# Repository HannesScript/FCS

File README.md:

# FCS - Flight Control System

This is a software designed for my own rocket's flight computer which is based on the ESP32-S3.

## Requirements:

- rust
- cargo
- espup - install with `cargo install espup && espup install`
- espflash - install with `cargo install espflash --version 3.3.0`

You can just run the [setup.sh](./setup.sh) file.

## Build & Flash:

You can just run [build_and_flash.sh](./build_and_flash.sh).

## Components:

- ESP32-S3
- BMP280
- MPU6050
- PCA9685
- nRF24L01
- Arduino (ESP32-S3) compatible SD-Card reader
- a GPS module (e.g. GY-GPS6MV2)
- 2x simple N-MOSFET (though please check if it is usable with a chip such as this)
- DHT11

## PCB:

All the files for the PCB and the schematics are located in the [pcb folder](./pcb/). These files are ready for manufacturing and usage.

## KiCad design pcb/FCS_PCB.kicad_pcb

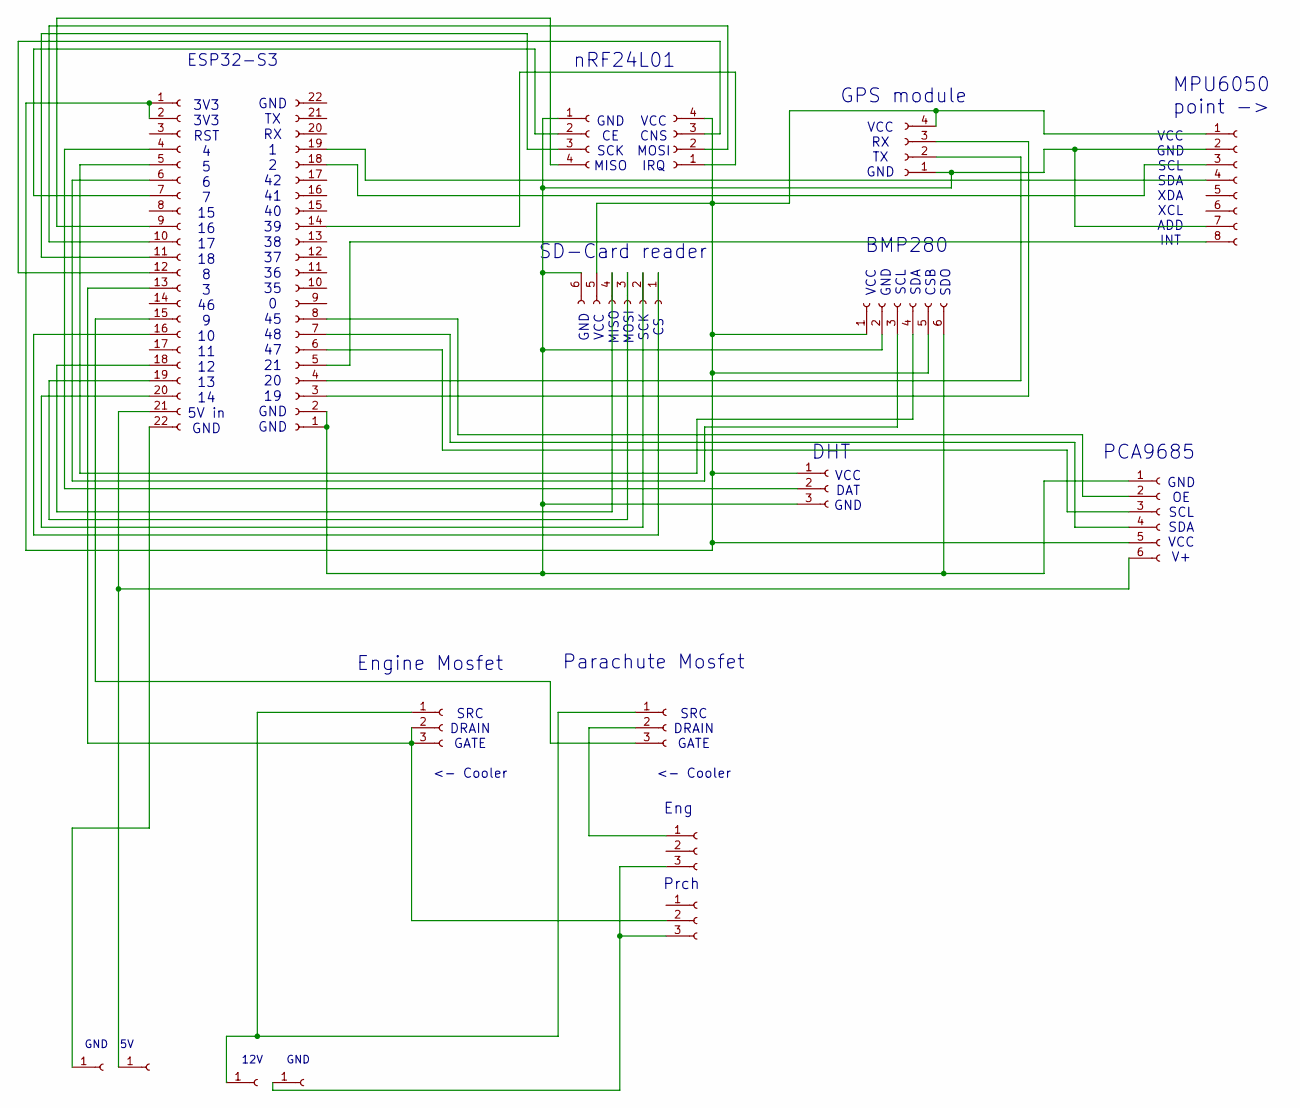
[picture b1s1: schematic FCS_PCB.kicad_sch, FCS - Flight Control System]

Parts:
J1, J2: Conn_01x22_Socket; PinSocket_1x22_P2.54mm_Vertical
J3, J4, J6: Conn_01x04_Socket; PinSocket_1x04_P2.54mm_Vertical
J5: PinSocket_1x06_P2.54mm_Vertical
J7, J10: Conn_01x06_Socket; PinSocket_1x06_P2.54mm_Vertical
J8: Conn_01x08_Socket; PinSocket_1x08_P2.54mm_Vertical
J9, J11, J12, J13, J14: Conn_01x03_Socket; PinSocket_1x03_P2.54mm_Vertical
J15, J16, J17, J18: Conn_01x01_Socket; PinSocket_1x01_P2.00mm_Vertical

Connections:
unnamed: J1.1, J1.2, J4.4, J5.5, J6.4, J7.1, J7.5, J8.1, J9.1, J10.5
unnamed: J1.4, J9.2
unnamed: J1.5, J7.4
unnamed: J1.6, J7.3
unnamed: J1.7, J3.2
unnamed: J1.9, J3.4
unnamed: J1.10, J4.2
unnamed: J1.11, J3.3
unnamed: J1.12, J4.3
unnamed: J1.13, J11.2, J11.3, J14.2
unnamed: J1.15, J12.3
unnamed: J1.16, J5.1
unnamed: J1.18, J5.4
unnamed: J1.19, J5.3
unnamed: J1.20, J5.2
unnamed: J1.21, J10.6, J16.1
unnamed: J1.22, J15.1
unnamed: J2.3, J6.3
unnamed: J2.4, J6.2
unnamed: J2.5, J8.8
unnamed: J2.14, J4.1
unnamed: J2.18, J8.3
unnamed: J2.19, J8.4
unnamed: J2.1, J2.2, J3.1, J5.6, J6.1, J7.2, J7.6, J8.2, J8.7, J9.3, J10.1
unnamed: J2.8, J10.2
unnamed: J2.6, J10.3
unnamed: J2.7, J10.4
unnamed: J11.1, J12.1, J17.1
unnamed: J12.2, J13.1
unnamed: J13.3, J14.3, J18.1

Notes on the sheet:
3V3 3V3 RST 4 5 6 7 15 16 17 18 8 3 46 9 10 11 12 13 14 5V in GND
nRF24L01
Parachute Mosfet
Eng
VCC GND SCL SDA XDA XCL ADD INT
VCC DAT GND
ESP32-S3
SD-Card reader
BMP280
GND CE SCK MISO
GPS module
GND OE SCL SDA VCC V+
Prch
VCC CNS MOSI IRQ
Engine Mosfet
12V GND
VCC GND SCL SDA CSB SDO
PCA9685
GND 5V
VCC RX TX GND
SRC DRAIN GATE <- Cooler
MPU6050 point ->
GND VCC MISO MOSI SCK CS
DHT
GND TX RX 1 2 42 41 40 39 38 37 36 35 0 45 48 47 21 20 19 GND GND

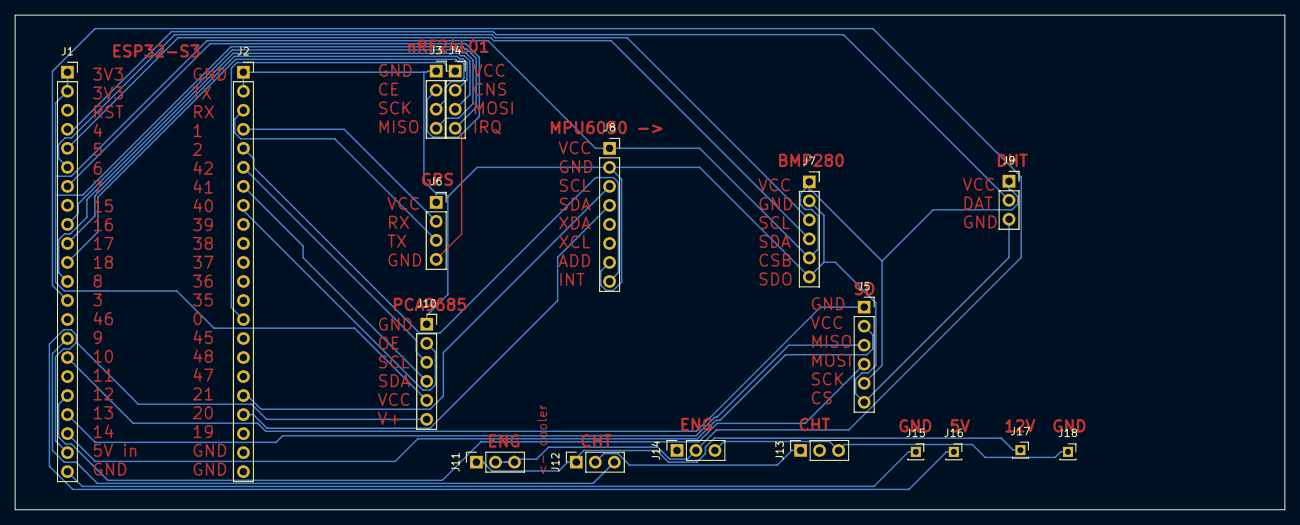
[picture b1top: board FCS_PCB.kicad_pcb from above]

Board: 2 copper layers, 169.5 x 66.0 mm, 18 parts (0 on the bottom side), 30 nets.

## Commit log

2026-03-14 added some structure and stubs
2026-03-15 Added some more stubs; some scripts and implemented some new logic
2026-03-16 updated README and added PCB files
